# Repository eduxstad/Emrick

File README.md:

# Emrick
 AAMB wearable light strip redesign

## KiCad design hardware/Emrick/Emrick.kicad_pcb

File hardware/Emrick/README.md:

# Emrick Hardware
This folder contains the KiCAD project of the wearable light strip PCB. 
In the production folder are the gerber and placement files for the latest 
revision, generated from KiCAD.

## Generating PCB production files
This process is meant for creating production files that will be used with JLCPCB.
For a different manufacturer the process may be slightly different. 

1. Install the [Fabrication Toolkit](https://github.com/bennymeg/JLC-Plugin-for-KiCad) plugin. This automates the PCB fabrication process. 
2. Once you've verified that the board has no unexpected errors in the electrical rules check and that the silkscreen is correct (any labels/versions updated, etc), press the fabrication button to generate the gerber and placement files in the production folder. 

Note that this will also create a bill of materials (BOM) for the PCB. However, the JLCPCB part numbers are not currently added to schematic (there are [instructions here](https://jlcpcb.com/help/article/81-How-to-generate-the-BOM-and-Centroid-file-from-KiCAD)) so the latest BOM is kept in `bom.xls`. 
3. Update the BOM file in `bom.xsl` with any new components and their JLCPCB part numbers. 
4. Order the boards from JLCPCB. Select 'Yes' -> 'JLC04161H-7628' as the Impedance Control and Layer Stackup options respectively. This is to select a specific material layup to preserve the RF characteristics of the PCB. 

## Hardware troubleshoot
Well, you're worried you toasted a board. Here are the steps to make sure that the board is happy. Note that for software/peripherals there is a Smoketest program in the `software/cc1310` folder that will test the functionality of all of the peripherals. 

1. If connected to USB, verify that you are receiving 5V from the VBUS connection. You can use the USB port shielding as ground, and touch the other end of the multimeter to pin 1 of C33. This can vary a few tenths of a volt due to what device you are connected to and how much current you are drawing. 

2. Verify the supply voltages of the CC1310 microcontroller. This is taken from section 12 of the Hardware and PCB Design considerations [here](https://www.ti.com/lit/an/swra640g/swra640g.pdf). 
    1. Verify the output of the regulator is 3.3 volts (aka VDDS == 3.3) on pin 2 of FB1. This should be within a tenth of a volt. 
  
    2. Verify that VDDR == 1.68 on pin 2 of L1. This should be within a 100th of a volt.
  
    3. Verify that DCOUPL == 1.27 on pin 1 of C22. This should be within a 10th of a volt. 
  
If these voltages check out, it's pretty likely that the CC1310 should be working correctly. 

3. Now we can move on to the boosted 5V LED output. 
    1. Load a program that turns on the LED lights, like SPIWS. Don't actually connect a light strip. 
    2. Check that the voltage on pin 1 of J1 is stable at 4.95V or greater. Ideally very close to 5V,like 4.99V, since there is only the extremely small load of the multimeter across it.

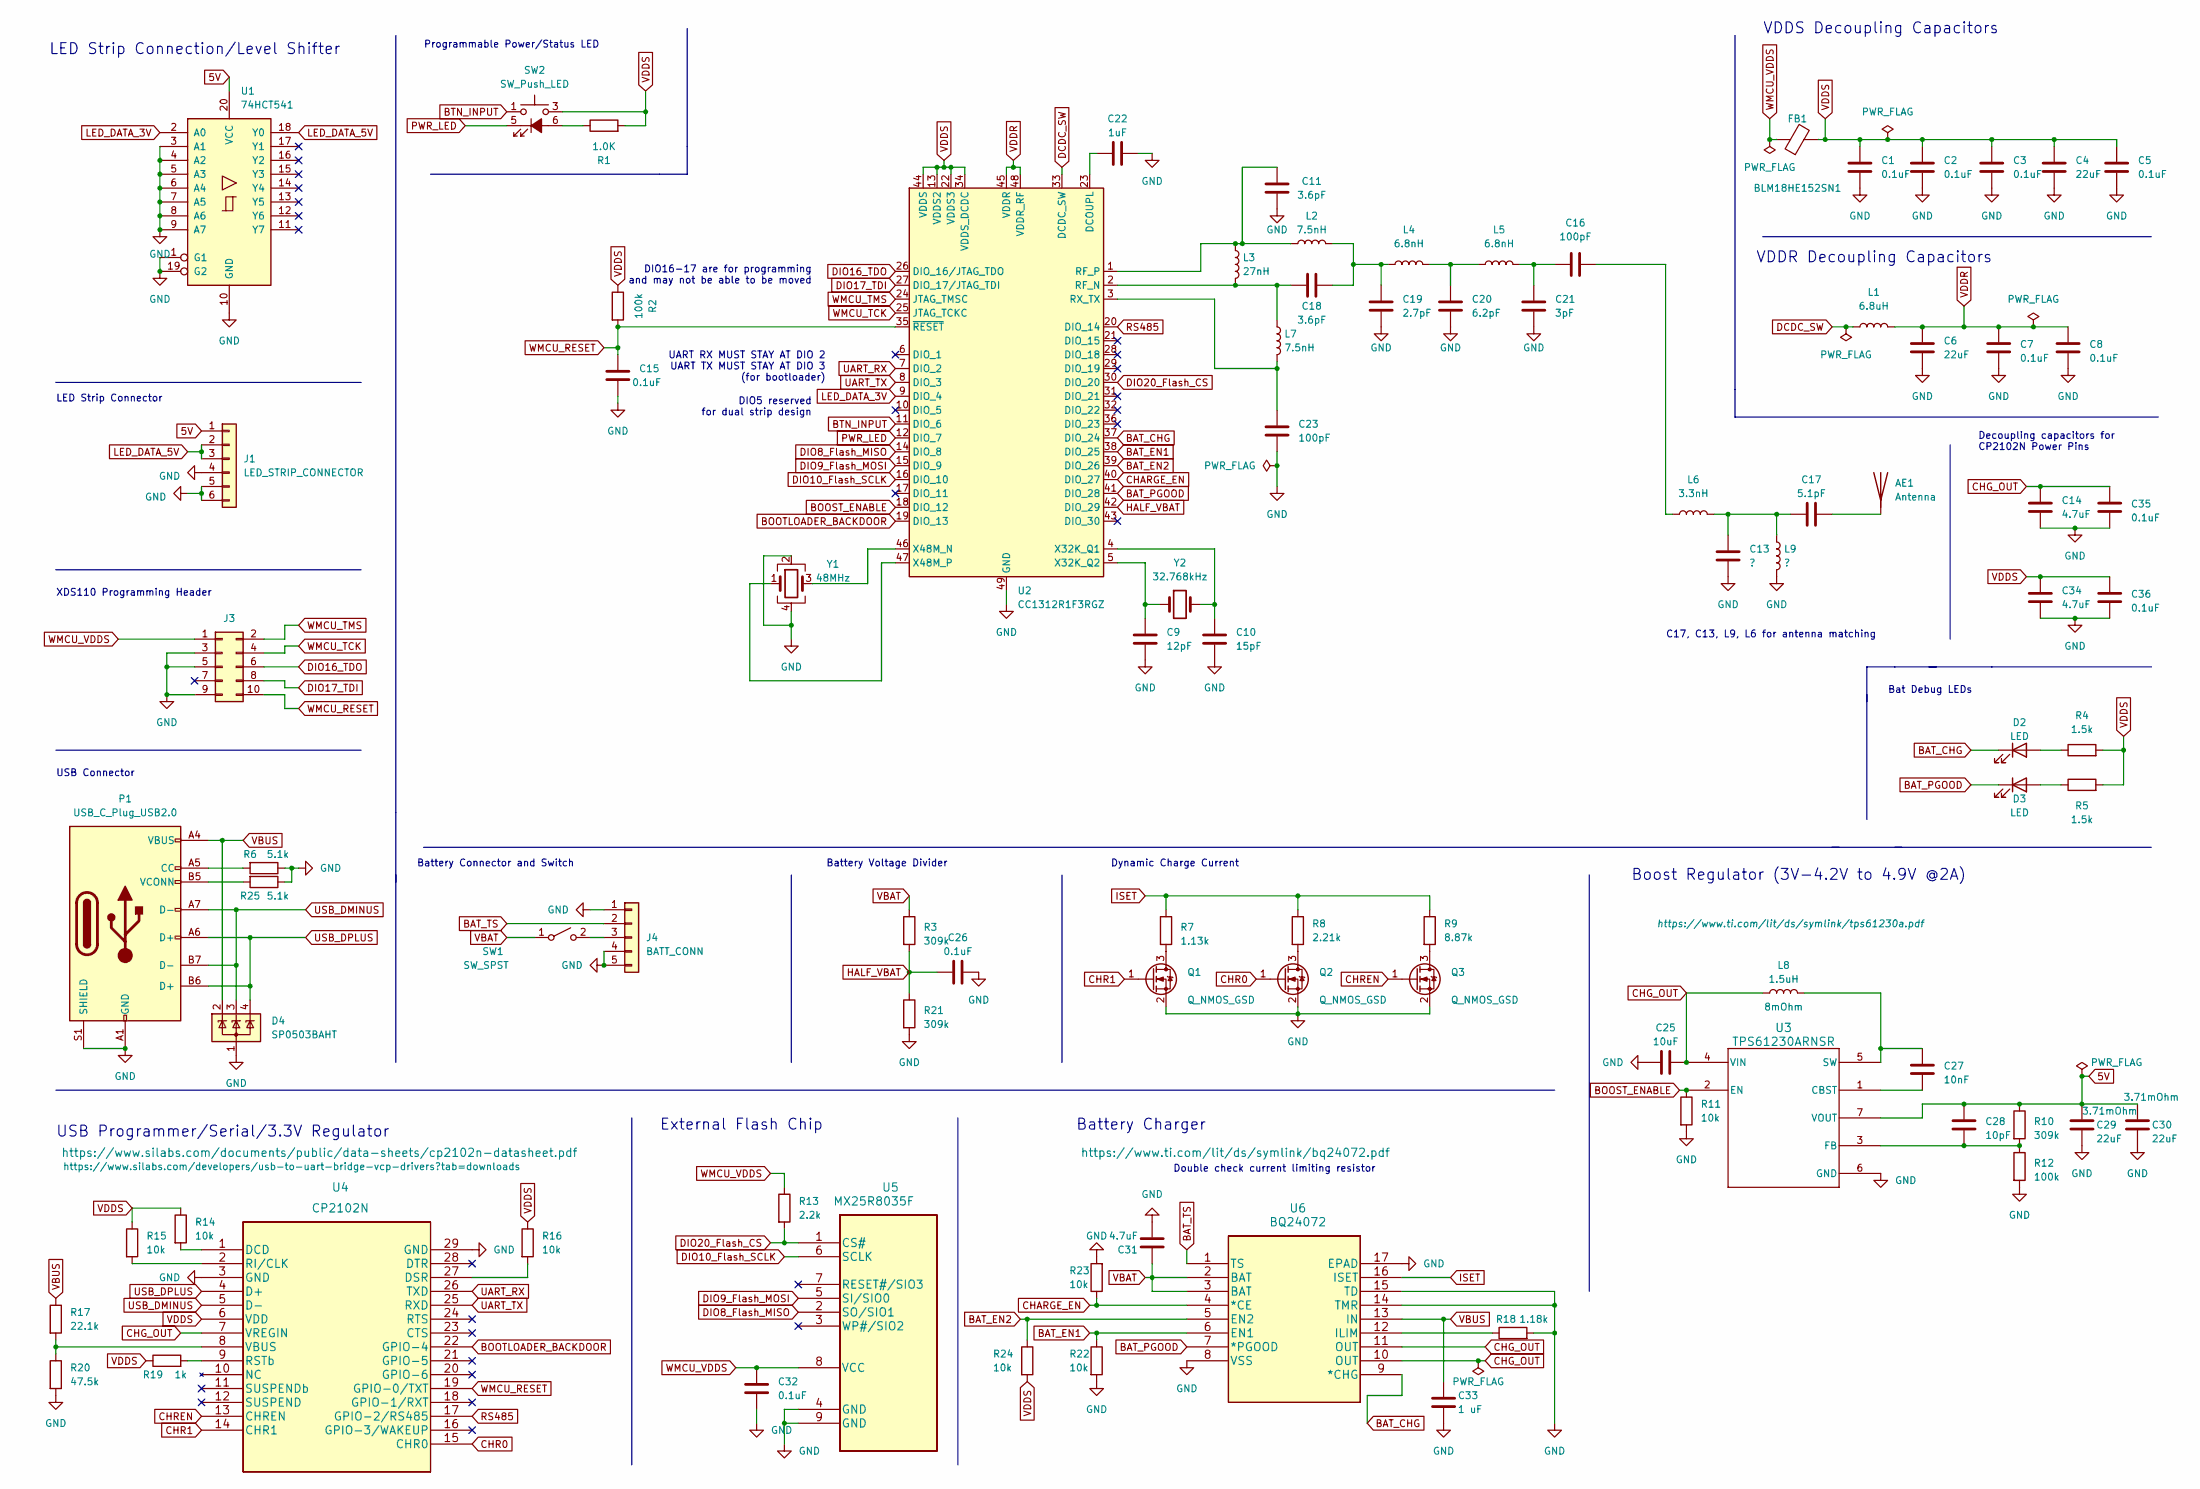
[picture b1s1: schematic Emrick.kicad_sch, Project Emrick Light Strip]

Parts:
AE1: Antenna; Texas_SWRA416_868MHz_915MHz
C1, C2, C3, C5, C7, C8, C15, C26, C32, C35, C36: 0.1uF; C_0402_1005Metric
C4, C6, C29, C30: 22uF; C_0603_1608Metric
C9: 12pF; C_0402_1005Metric
C10: 15pF; C_0402_1005Metric
C11, C18: 3.6pF; C_0402_1005Metric
C13: ?; C_0603_1608Metric
C14, C31, C34: 4.7uF; C_0402_1005Metric
C16, C23: 100pF; C_0402_1005Metric
C17: 5.1pF; C_0402_1005Metric
C19: 2.7pF; C_0402_1005Metric
C20: 6.2pF; C_0402_1005Metric
C21: 3pF; C_0402_1005Metric
C22: 1uF; C_0402_1005Metric
C25: 10uF; C_0603_1608Metric
C27: 10nF; C_0402_1005Metric
C28: 10pF; C_0402_1005Metric
C33: 1 uF; C_0402_1005Metric
D2, D3: LED; LED_0402_1005Metric
D4: SP0503BAHT; SOT-143
FB1: BLM18HE152SN1; R_0603_1608Metric
J1: LED_STRIP_CONNECTOR; CONN-SMD_SM04B-PASS-TBT-LF-SN
J3: Conn_02x05_Odd_Even; PinHeader_2x05_P1.27mm_Vertical
J4: BATT_CONN; DF65-3P-1.7V21
L1: 6.8uH; L_TDK_NLV32_3.2x2.5mm
L2, L7: 7.5nH; L_0402_1005Metric
L3: 27nH; L_0402_1005Metric
L4, L5: 6.8nH; L_0402_1005Metric
L6: 3.3nH; L_0402_1005Metric
L8: 1.5uH; L_Chilisin_BMRB00060612; MFR Part # BMMI000606301R5MX1
L9: ?; C_0603_1608Metric
P1: USB_C_Plug_USB2.0; USB_C_Receptacle_XKB_U262-16XN-4BVC11
Q1, Q2, Q3: Q_NMOS_GSD; SOT-23_Handsoldering
R1: 1.0K; R_0402_1005Metric
R2, R12: 100k; R_0402_1005Metric
R3, R10, R21: 309k; R_0402_1005Metric
R4, R5: 1.5k; R_0402_1005Metric
R6, R25: 5.1k; R_0402_1005Metric
R7: 1.13k; R_0603_1608Metric
R8: 2.21k; R_0603_1608Metric
R9: 8.87k; R_0603_1608Metric
R11, R14, R15, R16, R22, R23, R24: 10k; R_0402_1005Metric
R13: 2.2k; R_0402_1005Metric
R17: 22.1k; R_0402_1005Metric
R18: 1.18k; R_0402_1005Metric
R19: 1k; R_0402_1005Metric
R20: 47.5k; R_0402_1005Metric
SW1: SW_SPST; SW-TH_SS-12F45-GXXX
SW2: SW_Push_LED; SW-SMD_CHA_C603B-101ML-1SF
U1: 74HCT541; SN74HCT541PW
U2: CC1312R1F3RGZ; VQFN-48-1EP_7x7mm_P0.5mm_EP5.15x5.15mm
U3: TPS61230ARNSR; VQFN7_2X2_TEX
U4: CP2102N; CP2102N-A02-GQFN28
U5: MX25R8035F; MX25R8035FZUIL0
U6: BQ24072; BQ24072TRGTR
Y1: 48MHz; Crystal_SMD_3225-4Pin_3.2x2.5mm
Y2: 32.768kHz; Crystal_SMD_3215-2Pin_3.2x1.5mm

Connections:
5V: C28.2, C29.2, C30.1, J1.1, R10.1, U1.20 (VCC), U3.7 (VOUT)
BAT_CHG: D2.1 (K), U2.37 (DIO_24), U6.9 (*CHG)
BAT_EN1: R22.1, U2.38 (DIO_25), U6.6 (EN1)
BAT_EN2: R24.1, U2.39 (DIO_26), U6.5 (EN2)
BAT_PGOOD: D3.1 (K), U2.41 (DIO_28), U6.7 (*PGOOD)
BAT_TS: J4.2, U6.1 (TS)
BOOST_ENABLE: R11.1, U2.18 (DIO_12), U3.2 (EN)
BOOTLOADER_BACKDOOR: U2.19 (DIO_13), U4.22 (GPIO-4)
BTN_INPUT: SW2.1, U2.11 (DIO_6)
CHARGE_EN: R23.1, U2.40 (DIO_27), U6.4 (*CE)
CHG_OUT: C14.1, C25.2, C35.1, L8.1, U3.4 (VIN), U4.7 (VREGIN), U6.10 (OUT), U6.11 (OUT)
CHR0: Q2.1 (G), U4.15 (CHR0)
CHR1: Q1.1 (G), U4.14 (CHR1)
CHREN: Q3.1 (G), U4.13 (CHREN)
DCDC_SW: L1.1, U2.33 (DCDC_SW)
DIO8_Flash_MISO: U2.14 (DIO_8), U5.2 (SO/SIO1)
DIO9_Flash_MOSI: U2.15 (DIO_9), U5.5 (SI/SIO0)
DIO10_Flash_SCLK: U2.16 (DIO_10), U5.6 (SCLK)
DIO16_TDO: J3.6, U2.26 (DIO_16/JTAG_TDO)
DIO17_TDI: J3.8, U2.27 (DIO_17/JTAG_TDI)
DIO20_Flash_CS: R13.2, U2.30 (DIO_20), U5.1 (CS#)
GND: C1.2, C2.2, C3.2, C4.2, C5.2, C6.2, C7.2, C8.2, C9.2, C10.2, C11.1, C13.2, C14.2, C15.2, C19.2, C20.2, C21.2, C22.1, C23.2, C25.1, C26.1, C29.1, C30.2, C31.2, C32.2, C33.2, C34.2, C35.2, C36.2, D4.1 (A), J1.4, J1.5, J1.6, J3.3, J3.5, J3.9, J4.1, J4.4, J4.5, L9.2, P1.A1 (GND), P1.A12 (GND), P1.B1 (GND), P1.B12 (GND), P1.S1 (SHIELD), Q1.2 (S), Q2.2 (S), Q3.2 (S), R6.1, R11.2, R12.2, R18.2, R20.2, R21.2, R22.2, R23.2, R25.1, U1.1 (G1), U1.3 (A1), U1.4 (A2), U1.5 (A3), U1.6 (A4), U1.7 (A5), U1.8 (A6), U1.9 (A7), U1.10 (GND), U1.19 (G2), U2.49 (GND), U3.6 (GND), U4.3 (GND), U4.29 (GND), U5.4 (GND), U5.9 (GND), U6.8 (VSS), U6.14 (TMR), U6.15 (TD), U6.17 (EPAD), Y1.2, Y1.4
HALF_VBAT: C26.2, R3.2, R21.1, U2.42 (DIO_29)
ISET: R7.1, R8.1, R9.1, U6.16 (ISET)
LED_DATA_3V: U1.2 (A0), U2.9 (DIO_4)
LED_DATA_5V: J1.2, J1.3, U1.18 (Y0)
unnamed: AE1.1 (A), C17.2
unnamed: C13.1, C17.1, L6.2, L9.1
unnamed: C16.1, L6.1
unnamed: C16.2, C21.1, L5.2
unnamed: C18.2, C19.1, L2.2, L4.1
unnamed: C20.1, L4.2, L5.1
unnamed: D2.2 (A), R4.1
unnamed: D3.2 (A), R5.1
unnamed: J4.3, SW1.2 (B)
unnamed: P1.A5 (CC), R6.2
unnamed: P1.B5 (VCONN), R25.2
unnamed: Q1.3 (D), R7.2
unnamed: Q2.3 (D), R8.2
unnamed: Q3.3 (D), R9.2
unnamed: R1.1, SW2.6 (A)
unnamed: C22.2, U2.23 (DCOUPL)
unnamed: C18.1, L3.2, L7.1, U2.2 (RF_N)
unnamed: C11.2, L2.1, L3.1, U2.1 (RF_P)
unnamed: C23.1, L7.2, U2.3 (RX_TX)
unnamed: C10.1, U2.4 (X32K_Q1), Y2.2
unnamed: C9.1, U2.5 (X32K_Q2), Y2.1
unnamed: U2.46 (X48M_N), Y1.3
unnamed: U2.47 (X48M_P), Y1.1
unnamed: C27.2, U3.1 (CBST)
unnamed: C28.1, R10.2, R12.1, U3.3 (FB)
unnamed: C27.1, L8.2, U3.5 (SW)
unnamed: R14.2, U4.1 (DCD)
unnamed: R16.2, U4.27 (DSR)
unnamed: R15.2, U4.2 (RI/CLK)
unnamed: R19.2, U4.9 (RSTb)
unnamed: R17.2, R20.1, U4.8 (VBUS)
unnamed: R18.1, U6.12 (ILIM)
PWR_LED: SW2.5 (K), U2.12 (DIO_7)
RS485: U2.20 (DIO_14), U4.17 (GPIO-2/RS485)
UART_RX: U2.7 (DIO_2), U4.26 (TXD)
UART_TX: U2.8 (DIO_3), U4.25 (RXD)
USB_DMINUS: D4.3 (K), P1.A7 (D-), P1.B7 (D-), U4.5 (D-)
USB_DPLUS: D4.4 (K), P1.A6 (D+), P1.B6 (D+), U4.4 (D+)
VBAT: C31.1, R3.1, SW1.1 (A), U6.2 (BAT), U6.3 (BAT)
VBUS: C33.1, D4.2 (K), P1.A4 (VBUS), P1.A9 (VBUS), P1.B4 (VBUS), P1.B9 (VBUS), R17.1, U6.13 (IN)
VDDR: C6.1, C7.1, C8.1, L1.2, U2.45 (VDDR), U2.48 (VDDR_RF)
VDDS: C1.1, C2.1, C3.1, C4.1, C5.1, C34.1, C36.1, FB1.2, R1.2, R2.1, R4.2, R5.2, R14.1, R15.1, R16.1, R19.1, R24.2, SW2.3, U2.13 (VDDS2), U2.22 (VDDS3), U2.34 (VDDS_DCDC), U2.44 (VDDS), U4.6 (VDD)
WMCU_RESET: C15.1, J3.10, R2.2, U2.35 (~RESET), U4.19 (GPIO-0/TXT)
WMCU_TCK: J3.4, U2.25 (JTAG_TCKC)
WMCU_TMS: J3.2, U2.24 (JTAG_TMSC)
WMCU_VDDS: C32.1, FB1.1, J3.1, R13.1, U5.8 (VCC)

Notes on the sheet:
Dynamic Charge Current
Battery Charger
Double check current limiting resistor
LED Strip Connection/Level Shifter
VDDS Decoupling Capacitors
VDDR Decoupling Capacitors
LED Strip Connector
USB Connector
XDS110 Programming Header
USB Programmer/Serial/3.3V Regulator
C17, C13, L9, L6 for antenna matching
Programmable Power/Status LED
Bat Debug LEDs
Decoupling capacitors for CP2102N Power Pins
Boost Regulator (3V-4.2V to 4.9V @2A)
DIO5 reserved for dual strip design
Battery Connector and Switch
UART RX MUST STAY AT DIO 2 UART TX MUST STAY AT DIO 3 (for bootloader)
Battery Voltage Divider
External Flash Chip
DIO16-17 are for programming and may not be able to be moved

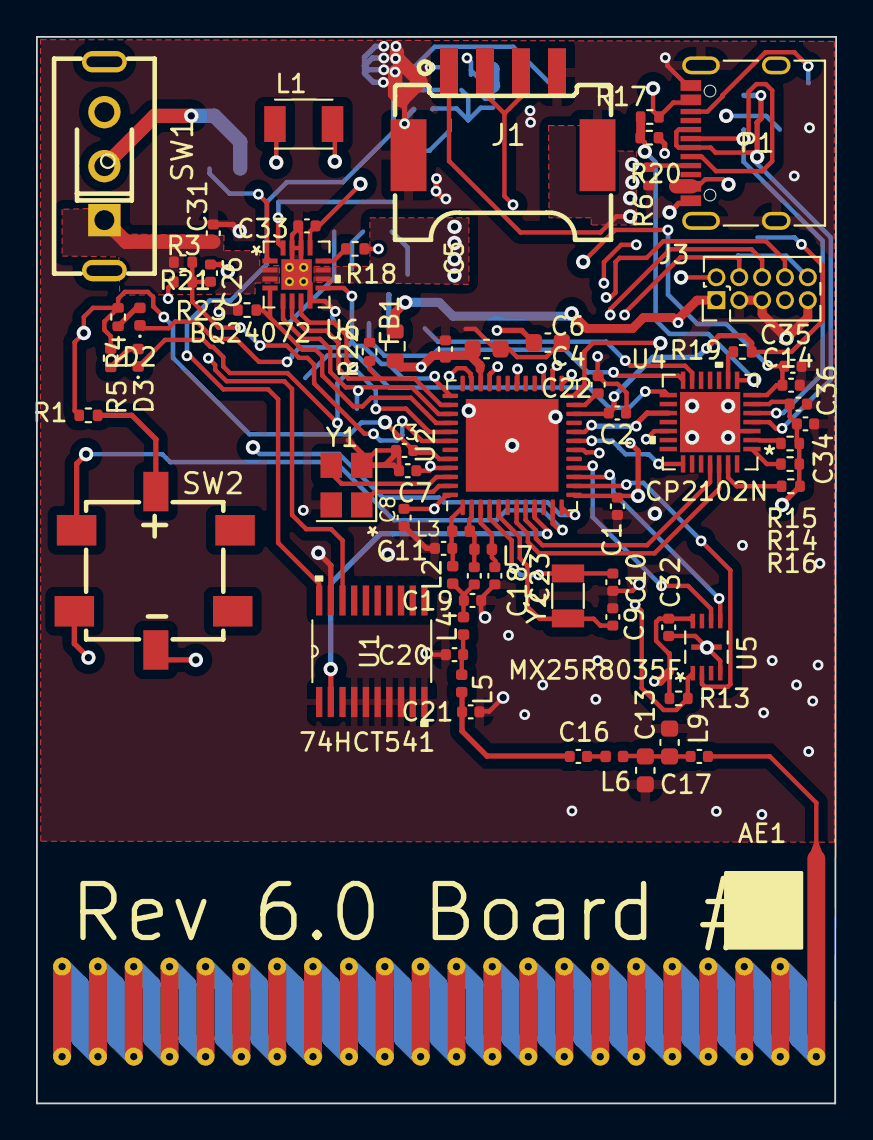
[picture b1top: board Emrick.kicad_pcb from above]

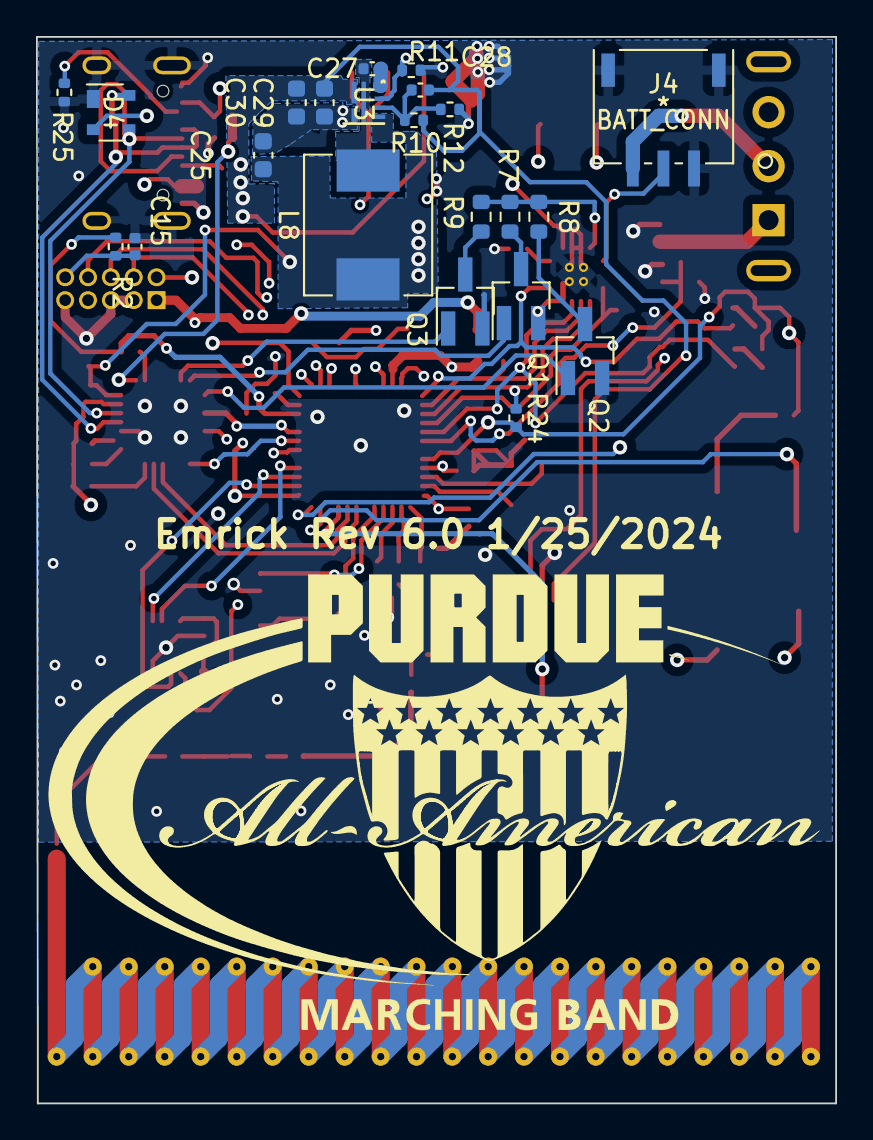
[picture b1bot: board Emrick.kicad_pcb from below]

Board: 4 copper layers, 44.4 x 59.2 mm, 90 parts (22 on the bottom side), 72 nets.

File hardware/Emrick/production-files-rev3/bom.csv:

Designator,Footprint,Quantity,Value,LCSC Part #
AE1,emrick_custom_antenna,1,Antenna,
"C1, C15, C2, C26, C3, C32, C35, C36, C5, C7, C8",0402,11,0.1uF,
C10,0402,1,15pF,
"C11, C18",0402,2,3.6pF,
C12,0402,1,?,
"C13, L9",0603,2,?,
"C14, C31, C34",0402,3,4.7uF,
"C16, C23",0402,2,100pF,
C17,0402,1,5.6pF,
C19,0402,1,2.7pF,
C20,0402,1,6.2pF,
C21,0402,1,3pF,
C22,0402,1,1uF,
C25,0603,1,10uF,
C27,0402,1,10nF,
C28,0402,1,10pF,
"C29, C30, C4, C6",0603,4,22uF,
C33,0402,1,1 uF,
C9,0402,1,12pF,
"D1, D2, D3",0402,3,LED,
D4,SOT-143,1,SP0503BAHT,
FB1,0603,1,BLM18HE152SN1,
J1,CONN_S4B-PH-SM4-TBLFSN_JST,1,LED_STRIP_CONNECTOR,
J2,U.FL_Hirose_U.FL-R-SMT-1_Vertical,1,UFL,
J3,PinHeader_2x05_P1.27mm_Vertical,1,Conn_02x05_Odd_Even,
J4,DF65-3P-1.7V21,1,BATT_CONN,
L1,L_TDK_NLV32_3.2x2.5mm,1,6.8uH,
"L2, L7",0402,2,7.5nH,
L3,0402,1,27nH,
"L4, L5",0402,2,6.8nH,
L6,0402,1,3.3nH,
L8,L_Chilisin_BMRB00060612,1,1.5uH,
P1,USB_C_Receptacle_XKB_U262-16XN-4BVC11,1,USB_C_Plug_USB2.0,
"Q1, Q2, Q3",SOT-23_Handsoldering,3,Q_NMOS_GSD,
"R1, R4, R5",0402,3,1.5k,
"R10, R21, R3",0402,3,309k,
"R11, R14, R15, R16",0402,4,10k,
"R12, R2",0402,2,100k,
R13,0402,1,2.2k,
R17,0402,1,22.1k,
R18,0402,1,1.18k,
R19,0402,1,1k,
R20,0402,1,47.5k,
R6,0402,1,5.1k,
R7,0603,1,1.13k,
R8,0603,1,2.21k,
R9,0603,1,8.87k,
SW1,SS-12D10G5_XKB,1,SW_SPST,
U1,SN74HCT541PW,1,74HCT541,
U2,CC1310F128RGZR,1,CC1310,
U3,VQFN7_2X2_TEX,1,TPS61230ARNSR,
U4,CP2102N-A02-GQFN28,1,CP2102N,
U5,MX25R8035FZUIL0,1,MX25R8035F,
U6,BQ24072TRGTR,1,BQ24072,
Y1,Crystal_SMD_3225-4Pin_3.2x2.5mm,1,24MHz,
Y2,Crystal_SMD_3215-2Pin_3.2x1.5mm,1,32.768kHz,

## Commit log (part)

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2022-08-11 add reference design
2022-08-11 add hardware files
2022-08-11 add software readme
2022-09-12 add rust tixml files and arduino examples
2022-09-12 Create sketch_sep08a.ino
    added demo for arduio LED strip
2022-09-12 add morsepoc_rx examples for arduino
2022-09-13 Button Test
2022-09-13 Prelim Demo Code
2022-09-14 update rs peripheral access library
2022-09-14 add feather 3d print box
2022-09-15 Templates provided for feather cases
2022-09-15 Successful demo
2022-09-15 Light-radio changes
2022-09-16 Working Code (One step back)
2022-09-19 add solidworks files and update gitignore
    I used the instructions from this link: https://grabcad.com/tutorials/how-to-convert-stl-to-sldprt to setup solidworks to automatically convert from STL to SLDPRT
2022-09-20 New Demos
2022-09-20 add pitcherserial
2022-09-20 update gitignore
2022-09-20 New demo patterns
2022-09-21 Update Emrick.kicad_sch
    Update schematic
2022-09-21 Updated CAD files
2022-09-21 added voltage regulator
2022-09-27 add components to schematic
2022-09-28 Update battery charger, status LEDs, and UFL connector
2022-09-29 update schematic with usb to serial component
    ignore the changes to the lightdemo files
2022-09-30 assign symbol numbers and start assigning footprints
2022-09-30 Update pcb file with basic tentative layout
2022-10-04 added antenna footprint
2022-10-04 fix pcb
2022-10-04 Revert "added antenna footprint"
    This reverts commit 1526e2c5d79b2dbdcb05d433e16ef35f6e915ff8.
2022-10-04 update schematic
2022-10-04 antenna inserted to pcb drawing
    Still need to determine what layer(s) antenna will be on
2022-10-04 deleted redundant files
2022-10-04 Antenna on top and bottom layer
    Need vias
2022-10-05 PCB progress update
    Antenna modified to closely match launchpad, all major ICs placed, & several capacitors/resistors/inductors have rough placement.
2022-10-05 SPI code transfer
2022-10-06 Prelim CC SPI code
2022-10-07 finished footprint placements
    put all PCB components in their preliminary positions, switched out NMOSFETs for NPN transistors, need tracing/planes
2022-10-07 update schematic and pcb
2022-10-11 Placement changes to the PCB and schematic
    some footprint updates too because I realized they didn't have them in the right size
2022-10-11 update pdf
2022-10-11 closer to finished placement
2022-10-11 update antenna footprint
2022-10-12 rotated LED header
2022-10-12 route power signals on pcb
2022-10-13 added traces
2022-10-13 added more traces
2022-10-13 update schematic pdf with new changes
2022-10-13 fix trace
2022-10-18 update pcb and schematic and add antenna development kit
2022-10-18 Rainbow code
2022-10-18 Old name
2022-10-19 added pullup to reset circuitry
2022-10-20 Revert "added pullup to reset circuitry"
    This reverts commit 352271496a808d8b1eb14a86bebbd64d10ea0814.
2022-10-20 first pass at pcb
2022-10-20 rev 1 of board
2022-10-20 Radio Head
2022-10-21 Separate functionality
2022-10-21 Started Patterns C file
2022-10-25 BETTER CODE (Ham)
2022-10-25 Current Patterns Code (Ham)
2022-10-27 add ccs files to .gitignore
2022-10-27 Added logo and USB-C port to box
2022-10-28 Updated prototype case with updated USB hole and battery holding components.
2022-11-01 V2 of case
2022-11-01 STL's updated for round 2 of printing
2022-11-03 Updating SPI and fixing git issues with CCS
2022-11-04 Array Rainbow Function (Prelim)
2022-11-05 correct pinout of UART for bootloader programming
2022-11-06 revisions to schematic (fixed battery polarity and vdd/regin)
2022-11-06 fixed PCB gremlins
2022-11-07 Prototype Box V2 Part and STL files
2022-11-08 STL's Updated
2022-11-08 added battery charger bypass (Zareef)
2022-11-09 Flash memory (Prelim)
2022-11-09 add documents for hardware review
2022-11-10 modifications to pcb
2022-11-10 update SPI for PCB, change mainthread to spin instead of exit
2022-11-11 made the USB chip the regulator instead of battery charger, need to update PCB still
2022-11-11 some work on pcb and schematic
2022-11-14 update pcb with preliminary board revisions
2022-11-16 updated schematic
    replaced BJTs with nMOSFETs, set power supply of B/B regulator and VREGIN of USB chip to CHG_OUT (battery charger output)
    STILL NEED:
    A way to disable B/B regulator
2022-11-16 SPI and Flash working together
2022-11-17 Update schematic with rev 2 changes
    Add extra capacitors to power pins on CP2102N
    Add boost enable pin to micro
2022-11-17 V3 Packaging
2022-11-17 STLs added for printing
2022-11-18 revert unecessary changes to PCB
2022-11-18 revision 2
2022-11-18 bb reg input cap size change
2022-11-18 Revert "bb reg input cap size change"
    This reverts commit f62a5bffcea21d6105bda4ee1b458a6a36c878c0.
2022-11-18 update with bigger cap
2022-11-18 Flash code done (Actual Push)
2022-11-30 Updated SPI rate and code for dev board tx/rx
2022-11-30 Packaging V4
2022-12-02 STL files for new board. Sending to shop to be printed
2022-12-02 Animation Code
    Sick
2022-12-05 Quality Changes
2022-12-05 Radio SPI (Sending Arrays)
2022-12-06 Patterns through Radio
2022-12-08 Performance & Programming
2022-12-08 Board IDs Added
2022-12-08 Two different IDs
2022-12-08 Updated UART
2022-12-08 update SPIWS to be continuous
2023-05-18 update to kicad 7
2023-05-19 switch to rev 2 rx and tx pins
2023-05-20 Add battery voltage detection circuit and datasheets
    I probably won't be keeping the battery voltage detection circuit because it's not necessary as we can use the built in battery monitor
2023-05-23 add battery monitor and receiver
    These sample project were created to demonstrate and test the ability of the cc1310 to monitor the battery voltage. The Battery Monitor project is a modified version of SPIWS that creates a second th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
2023-05-24 3rd rev schematic
    Removed Reset Switch
    Changed to 61230 boost regulator for improved efficiency
    Reduced ISET resistance to increase charging speed to 1.3A
    Added pull down resister to Boost enable signal
    Added battery voltage divider for measuring battery voltage
    Added new connector footprint for LED strip (JST 4PIN surface mount)
2023-05-24 update revision number
2023-05-25 add revision 3 gerber files
2023-05-25 move rev 2 production files to their own folder
2023-06-28 Create readme for software folder
    include notes on how to generate hex image files
2023-07-06 Update FlashMemory project for revision 3+
2023-07-06 Add non-static definition for rainbowAnimation function
2023-07-06 Update software readme with project descriptions
2023-07-06 Add revision 3 fabrication files
2023-07-30 Finalize revision 4
    - Added rev4 bom
    - Updated production files in hardware\Emrick\production
    - Fixed/ignored all errors in board PCB
    - Added AAMB graphics
    - Changed connector to JST PA 4 pin for mechanical latch
2023-08-15 switch to 500mhz for wireless monitor monitor
2023-08-20 Add production files for revision 4.1
2023-08-20 Update label and switch to an in-stock oscillator
2023-09-04 Add supply and battery voltage monitor to smoketest outupt
2023-09-05 Hardware modifications for rev 5
    - Added control for battery charging to the microcontroller by connecting
    CHARGE_ENABLE, BAT_EN1, and BAT_EN2 to pins on the micro.
    - Modified the USB connector and schematic to support bidirectional USB insertion.
2023-09-10 Add instructions for how to create the production files and how to verify the voltages on the PCB
2023-09-10 fix nested lists
2023-09-10 fix J1 5v image
2023-09-25 added timer to receiver for debugging
2023-09-26 updated pattern and transmitter to fit new test steps
2023-09-28 updated rf and patterns so rf signals can be repeated
    allowing rf signals to be repeated should increase the probability of the signal reaching the receivers at long range
2023-09-28 update pattern timings
2023-09-28 Updated rf settings to hopefully increase range
2023-09-28 corrected rf settings
2023-09-29 extended test duration
2023-10-10 Revision 5.1
    - Switch to vertical smaller batter switch
    - Add LED power button that is connected to the cc1310
2023-10-14 old csv position files and data recordings
    Previously *.csv was in the .gitignore file. After removing it, I realized there are a bunch of files that I never added to the repo.
2023-10-19 filesystem cleanup
2023-10-19 project renaming
2023-10-20 update Software README
2023-10-20 Battery Monitor now reads accurate voltage
2023-10-24 extended battery monitoring delay
2023-10-24 implemented battery testing receiver
2023-10-24 delay change
2023-10-24 correct packet parsing
2023-10-26 Revert "delay change"
    This reverts commit 710185d4d241a7f1634de85e284945f2941e3a22.
2023-10-26 Revert "modifications to receiver for battery testing"
    This reverts commit 66d5141cc855d1bd85b7c14142e42ced0e2b5145.
2023-10-31 FIX: Packet, ADD: Valid patterns
    - Packet struct is now specified with fields (_setNum, _footer). Might get away without size field, but we'll see...
    - Pattern macros added for when R/W from saved show (either from file or from memory).
    - Removed function pointers
2023-11-03 Rotated battery and JST connectors, button not connected
2023-11-03 Centered LED button
2023-11-03 added onboard logging
2023-11-03 fixed obvious type errors in logger
2023-11-03 current progress for logging upon receiving a packet
    receiver still crashes when attempting to create a log and I'm currently unsure why. the transmitter, however, is functional
2023-11-04 Replaced SW1
2023-11-04 Updates from Erik (not all)
2023-11-04 Added fab files
2023-11-04 rev5.2 production files
2023-11-04 Updated gerbers with 5.2 silkscreen
2023-11-05 Updated formats for bom and pos
2023-11-05 Removed blind vias
2023-11-13 Use correct ADC for measuring the battery voltage
2023-11-20 add correct close function to smoketest
2023-11-20 format code
2023-11-27 Multithreading "prototype" function
    - Added main_func(), where 4 threads are spawned (will need to verify 4 threads spawn)
    - Removed defunct array of function pointers
2023-11-29 made thread attributes global
2023-11-29 unbroke the transmitter
2023-12-01 Bare minimum code
2023-12-01 update delay
2023-12-01 fixed attr error
2023-12-01 final pattern update
2023-12-01 update light count
2023-12-02 added off pattern
2023-12-12 Add 50 second sample to autoledshutoff
2023-12-22 Added Emrick 2 schematic files
2023-12-22 Moved Emrick 2 folder
2023-12-26 Updated power flags and decoupling capacitors for 5V and gnd
2023-12-28 restructured files and added new light pattern logic
2023-12-31 improved documentation on all major files
2023-12-31 updated readme and downloaded more storage
2024-01-16 update light pattern
2024-01-16 removed deprecated light functions
2024-01-22 added busy-waiting sleep function and support for converting patterns to bytes
2024-01-23 Moved inductor
2024-01-23 Moved inductor away from connector
2024-01-25 Start of rev 6.0
2024-01-25 Started connecting pins for rev 6.0
2024-01-26 Connected more pins for rev 6.0
2024-01-26 Added 1312 to pcb layout
2024-01-26 Fixed pin errors on pcb for cc1312
2024-01-26 Bom file rev 6.0
2024-01-26 Updated bom file with 1312 info
2024-01-29 Added 48MHz oscillator
2024-01-29 created new projects for rf test
2024-01-29 completed test??? (needs testing)
2024-01-30 update test ability
    added functionality for a rev4 board to run a light near a receiver and made the test more robust to packet drops at the end of a sequence
2024-01-30 removed redundant code
2024-01-30 rebuilt the ghost of hsv past
2024-01-30 non shift code too
2024-02-05 refactored the flags and created timeout function

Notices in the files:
parts and their libraries:
Copyright 2021 Accelerated Designs. All rights reserved.
